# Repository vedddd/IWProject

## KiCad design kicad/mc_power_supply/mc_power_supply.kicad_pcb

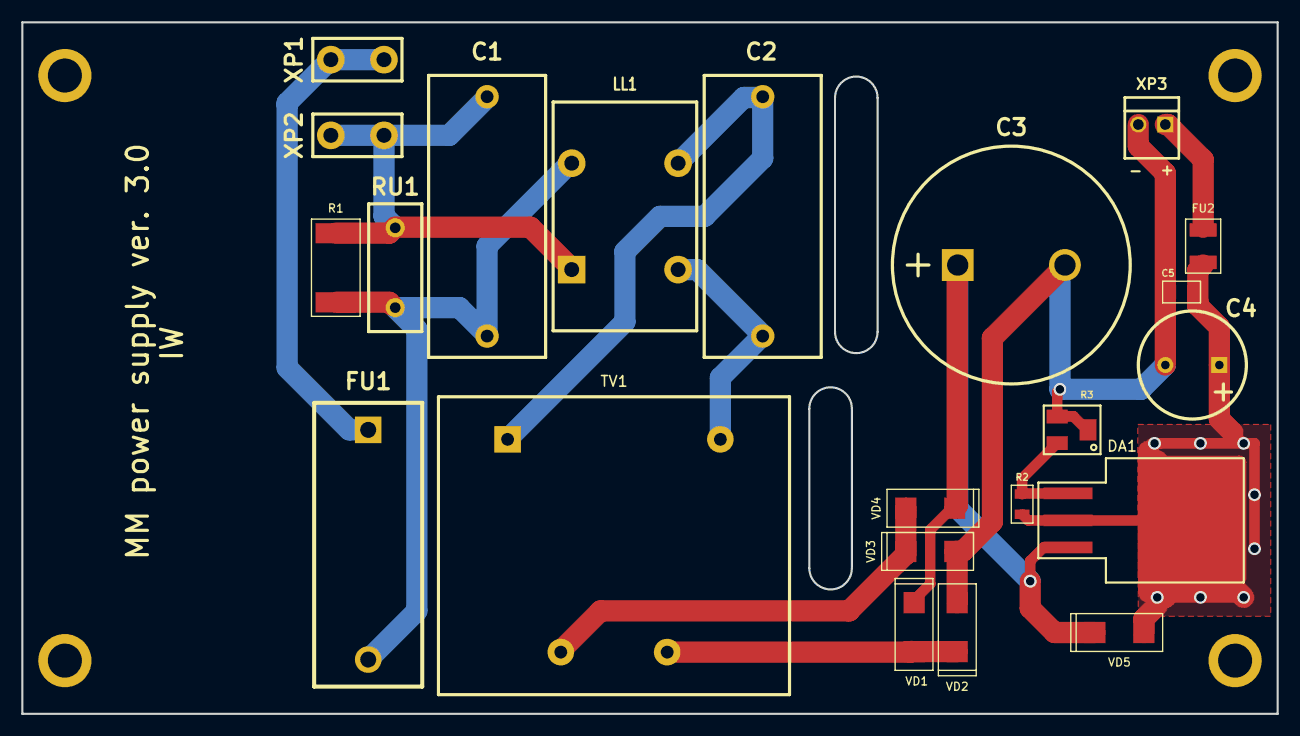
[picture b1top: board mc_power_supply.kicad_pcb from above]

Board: 2 copper layers, 118.0 x 65.0 mm, 26 parts (0 on the bottom side), 12 nets.

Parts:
1_PIN, 1_PIN#2, 1_PIN#3, 1_PIN#4: P***; 1_pin
C1, C2: 1 мк 305В; CAPACITOR_B32923_26.5x11
C3: 4700 мк 35 В; CAPACITOR_10_D22
C4: 470 мк 35 В; CAPACITOR_5.08_D10
C5: 0.1 мк; SMD0805
DA1: LM317KTTR; TO-263-3_TabPin_2
FU1: 0.1 A; FU_PTF15B
FU2: MF-USMF020-2; SMD1210
LL1: B82731T2301A020; EMI_EPCOS_B82731T
R1: 510 к; SMD2512
R2: 240; SMD0805
R3: 5 к; BOURNS_3224W
RU1: B72210S0271K101; RU_EPCOS_B72210S0271K101_12х5
TV1: ТПГ-2-12; TPG2-12
VD1, VD2, VD3, VD4, VD5: VS-10MQ100NTRPBF; SMA
XP1, XP2: L-KLS8-01128-PC-250-0.8; TERMINAL_KLS8-01128_6.3mm
XP3: WF-2

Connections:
/GND: C3.2, C4.2, C5.2, R3.2, R3.3, VD2.1, VD3.1, XP3.2
unnamed: C1.1, FU1.2, LL1.2, R1.2, RU1.1
unnamed: C1.2, LL1.1, R1.1, RU1.2, XP2.1
unnamed: C2.1, LL1.4, TV1.5
unnamed: C2.2, LL1.3, TV1.1
unnamed: C3.1, DA1.3, VD1.2, VD4.2, VD5.2
unnamed: C4.1, C5.1, DA1.2, FU2.1, R2.2, VD5.1
unnamed: DA1.1, R2.1, R3.1
unnamed: FU1.1, XP1.1
unnamed: FU2.2, XP3.1
unnamed: TV1.7, VD1.1, VD2.2
unnamed: TV1.9, VD3.2, VD4.1

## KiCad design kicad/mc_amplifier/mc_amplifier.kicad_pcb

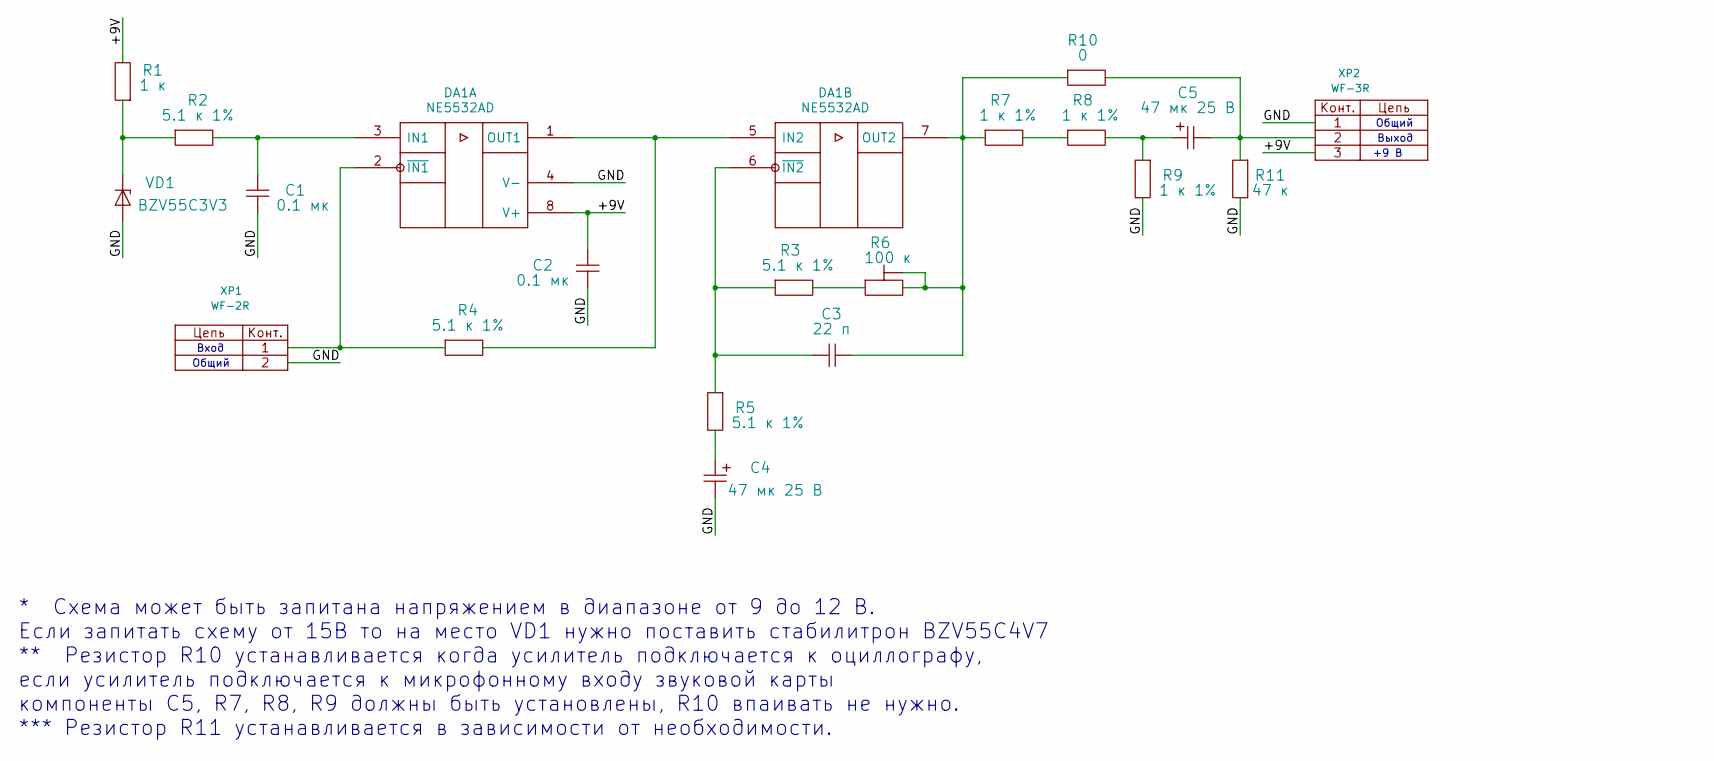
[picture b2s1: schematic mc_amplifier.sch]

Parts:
C1, C2: 0.1 мк; SMD0805
C3: 22 п; SMD0805
C4, C5: 47 мк 25 В; CASE_D
DA1: NE5532AD; SOIC8
R1: 1 к; SMD0805
R2, R3, R4, R5: 5.1 к 1%; SMD0805
R6: 100 к; BOURNS_3224J
R7, R8, R9: 1 к 1%; SMD0805
R10: 0; SMD0805
R11: 47 к; SMD0805
VD1: BZV55C3V3; SOD80C
XP1: WF-2R; WF-2
XP2: WF-3R; WF-3

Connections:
/+9V: C2.1, DA1.8 (V+), R1.2, XP2.3
/GND: C1.2, C2.2, C4.2, DA1.4 (V-), R9.2, R11.2, VD1.1, XP1.2, XP2.1
unnamed: C1.1, DA1.3 (IN1), R2.2
unnamed: C3.1, DA1.7 (OUT2), R6.2, R6.3, R7.1, R10.1
unnamed: C3.2, DA1.6 (~IN2), R3.1, R5.1
unnamed: C4.1, R5.2
unnamed: C5.1, R8.2, R9.1
unnamed: C5.2, R10.2, R11.1, XP2.2
unnamed: DA1.1 (OUT1), DA1.5 (IN2), R4.2
unnamed: DA1.2 (~IN1), R4.1, XP1.1
unnamed: R1.1, R2.1, VD1.2
unnamed: R3.2, R6.1
unnamed: R7.2, R8.1

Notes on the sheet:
Вход
Общий
Выход
+9 В
* Схема может быть запитана напряжением в диапазоне от 9 до 12 В. Если запитать схему от 15В то на место VD1 нужно поставить стабилитрон BZV55C4V7 ** Резистор R10 устанавливается когда усилитель подключается к оциллографу, если усилитель подключается к микрофонному входу звуковой карты компоненты C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

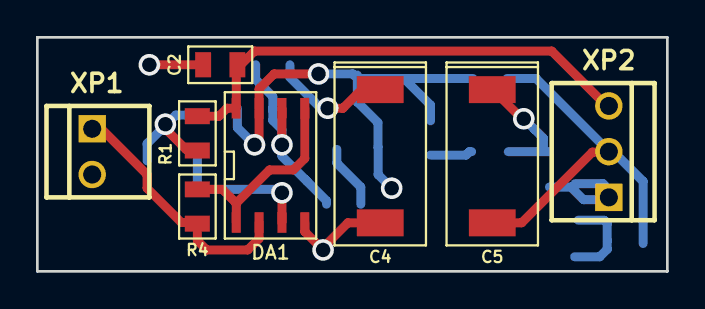
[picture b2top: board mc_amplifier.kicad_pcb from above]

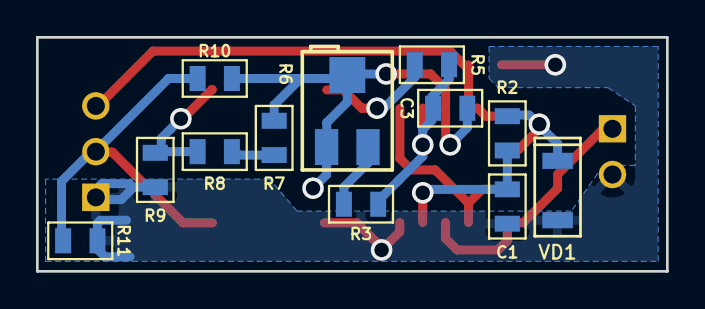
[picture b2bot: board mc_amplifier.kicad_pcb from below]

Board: 2 copper layers, 35.0 x 13.0 mm, 20 parts (12 on the bottom side), 13 nets.

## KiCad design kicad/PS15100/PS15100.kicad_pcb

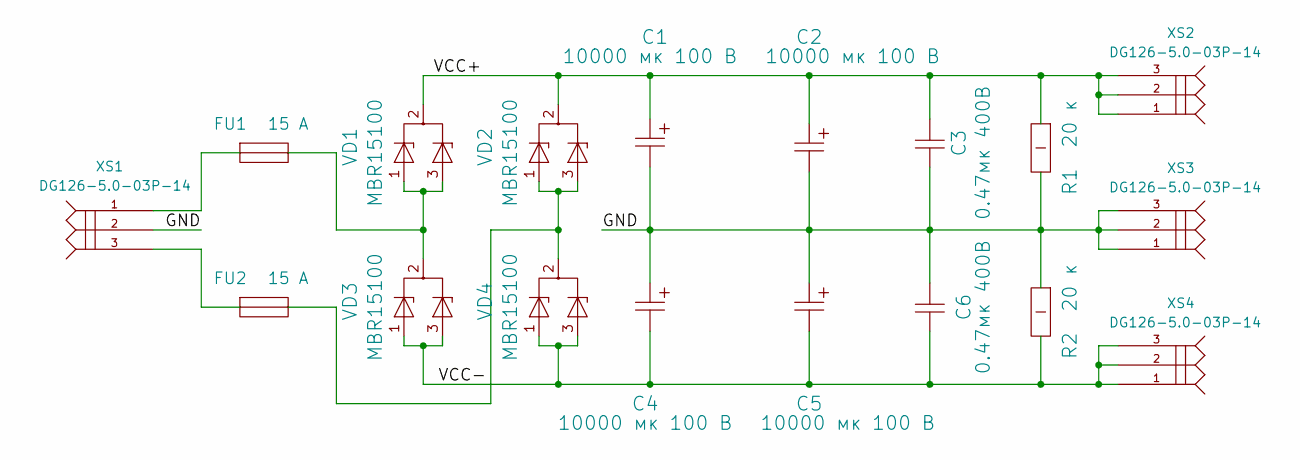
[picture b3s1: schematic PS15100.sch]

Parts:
C1, C2, C4, C5: 10000 мк 100 В; CAPACITOR_10_D36
C3, C6: 0.47мк 400В; K73-17
FU1, FU2: 15 A; FU_PTF15B
R1, R2: 20 к; RESISTOR_1W
VD1, VD2, VD3, VD4: MBR15100; TO220_RAD_16.5x15_VD
XS1, XS2, XS3, XS4: DG126-5.0-03P-14

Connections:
/GND: C1.2, C2.2, C3.1, C4.1, C5.1, C6.2, R1.2, R2.1, XS1.2, XS3.1, XS3.2, XS3.3
/VCC+: C1.1, C2.1, C3.2, R1.1, VD1.2, VD2.2, XS2.1, XS2.2, XS2.3
/VCC-: C4.2, C5.2, C6.1, R2.2, VD3.1, VD3.3, VD4.1, VD4.3, XS4.1, XS4.2, XS4.3
unnamed: FU1.1, XS1.1
unnamed: FU1.2, VD1.1, VD1.3, VD3.2
unnamed: FU2.1, XS1.3
unnamed: FU2.2, VD2.1, VD2.3, VD4.2

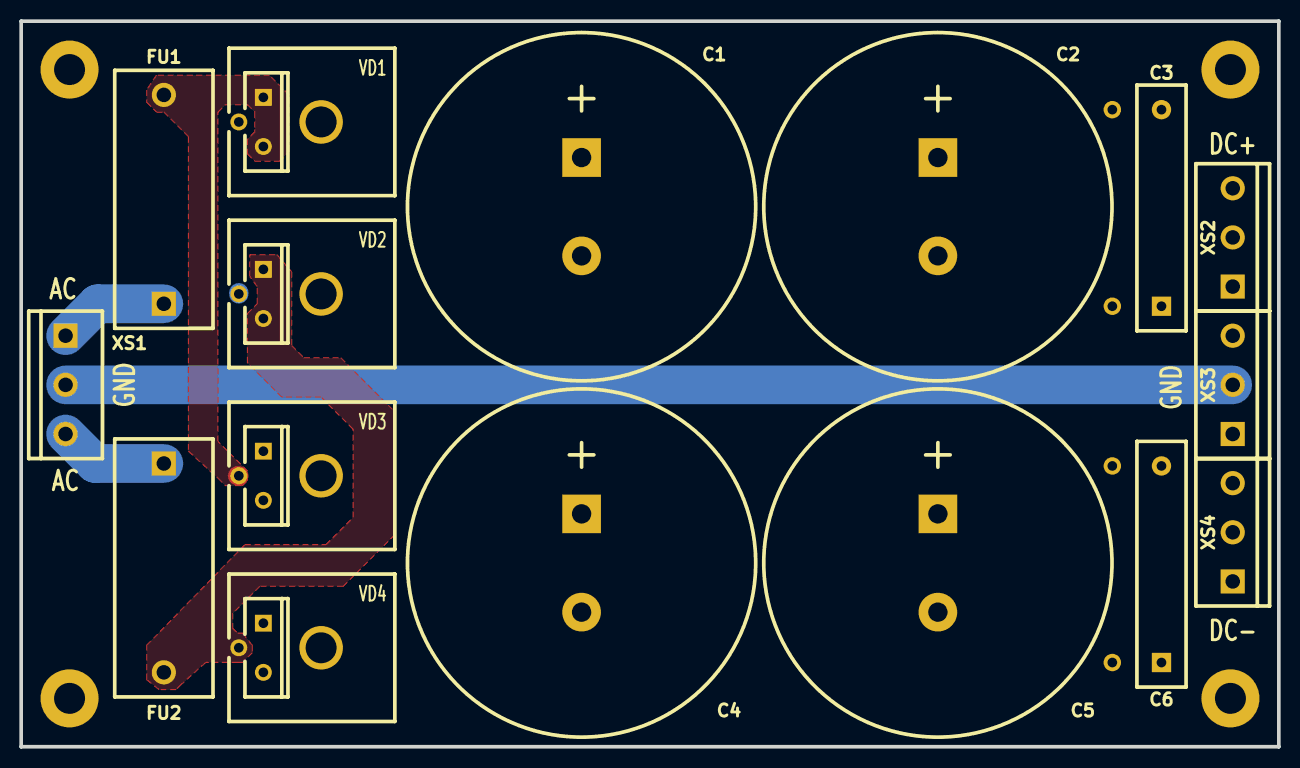
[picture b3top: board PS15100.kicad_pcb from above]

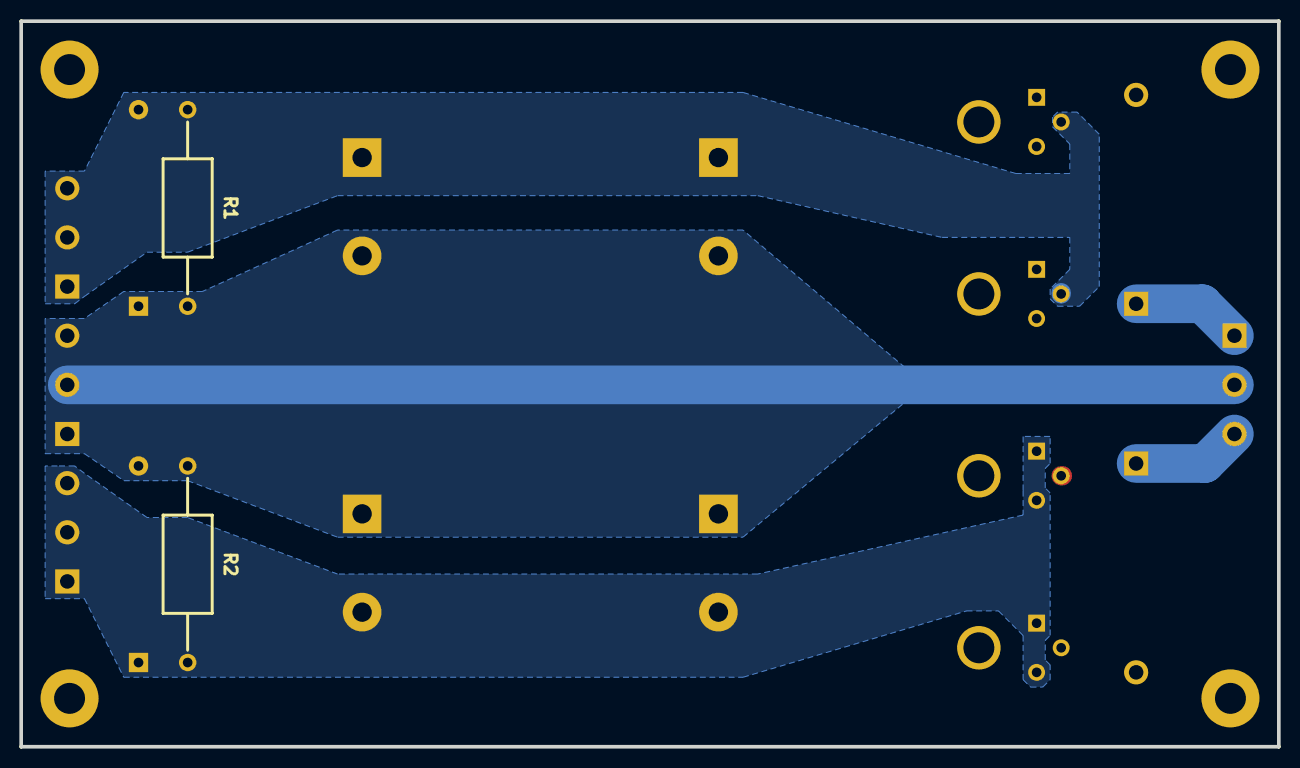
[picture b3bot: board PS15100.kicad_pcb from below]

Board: 2 copper layers, 130.0 x 75.0 mm, 22 parts (2 on the bottom side), 7 nets.

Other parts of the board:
1_PIN, 1_PIN#2, 1_PIN#3, 1_PIN#4: P***; 1_pin

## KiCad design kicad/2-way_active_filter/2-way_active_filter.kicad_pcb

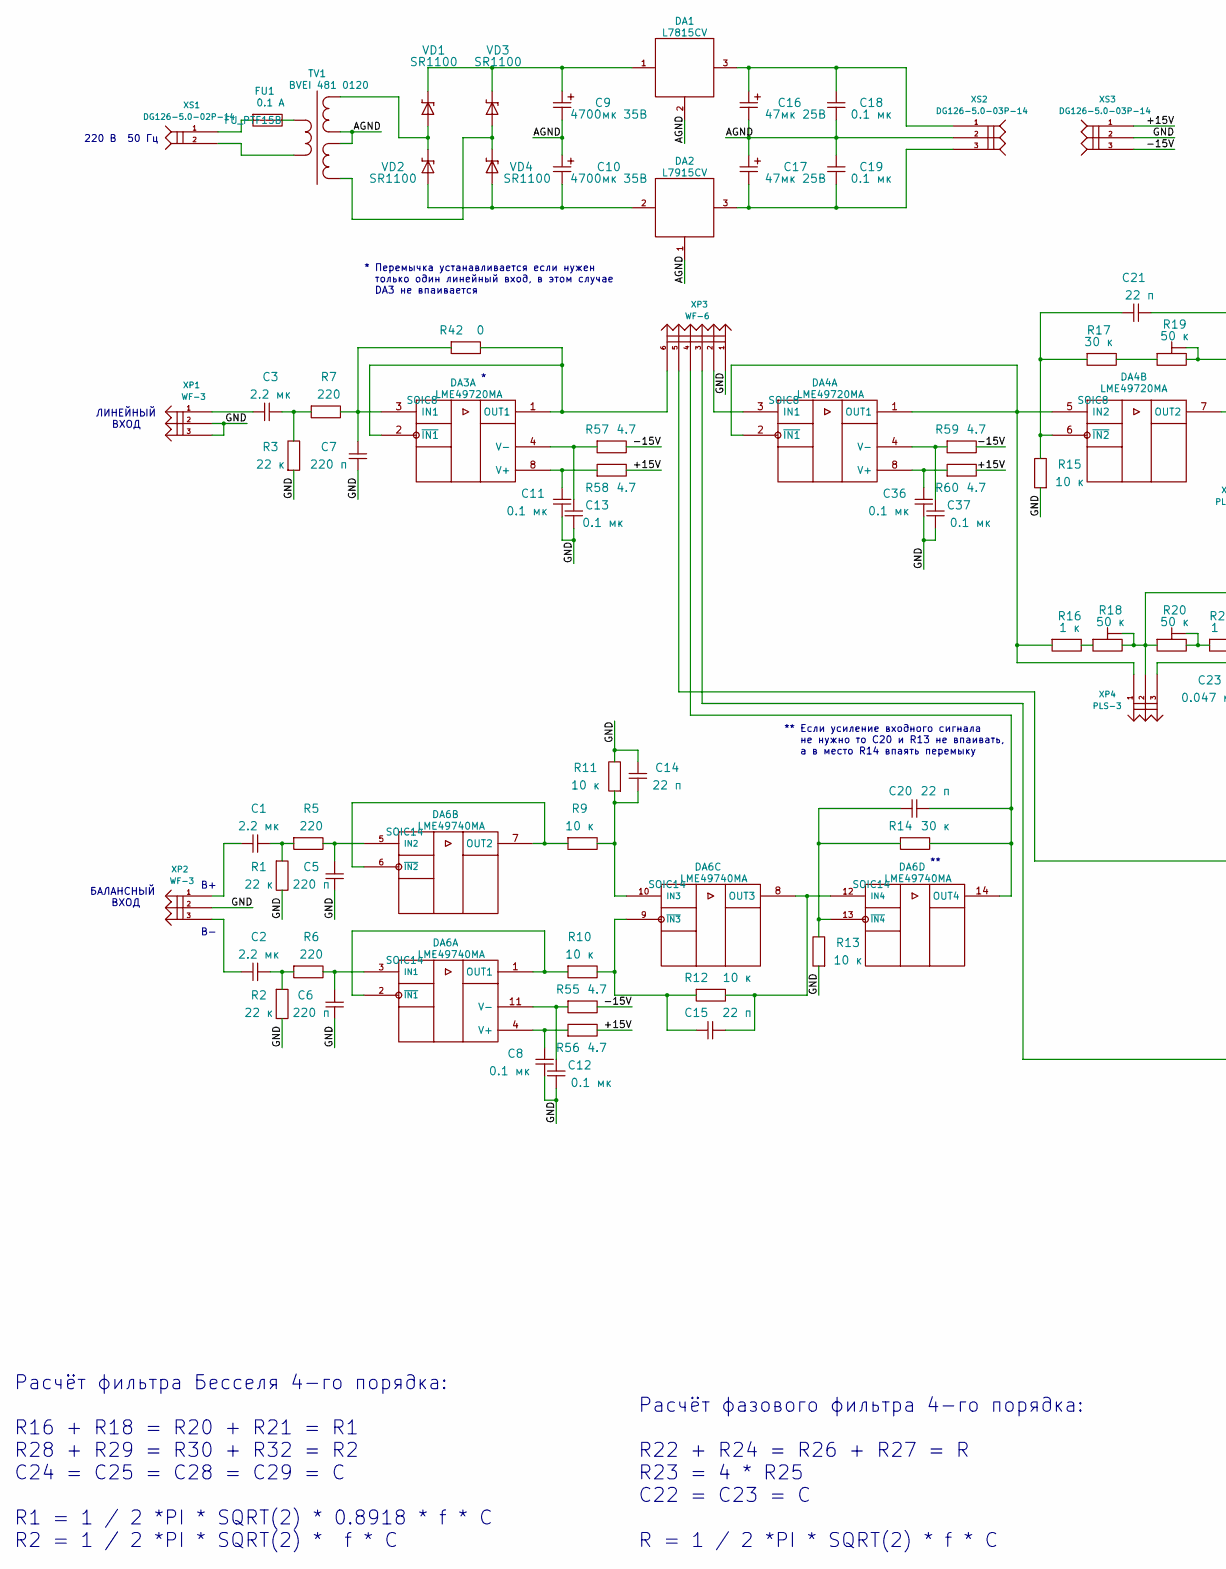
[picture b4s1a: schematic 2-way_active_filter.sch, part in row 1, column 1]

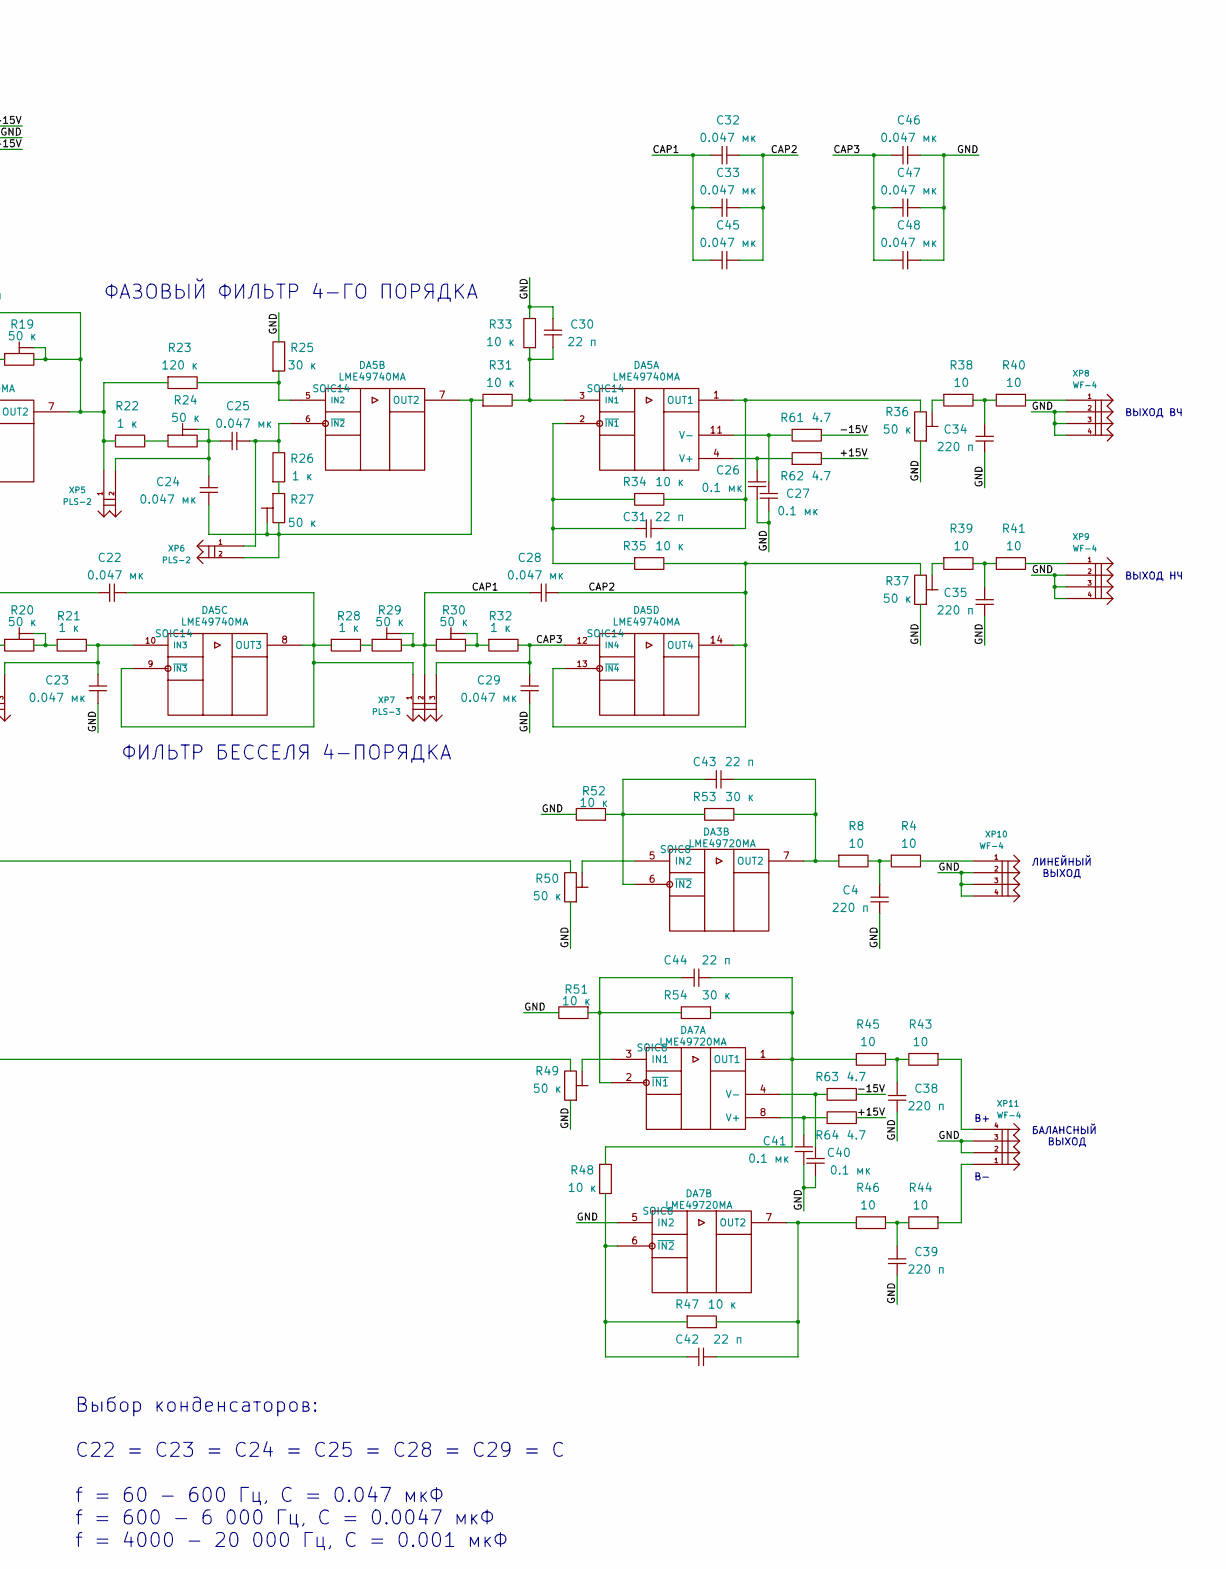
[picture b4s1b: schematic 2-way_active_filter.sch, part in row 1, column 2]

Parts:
C1, C2, C3: 2.2 мк; CAPACITOR_MKP4_27_5_32x11
C4, C5, C6, C7, C34, C35, C38, C39: 220 п; SMD0805
C8, C11, C12, C13, C18, C19, C26, C27, C36, C37, C40, C41: 0.1 мк; SMD0805
C9, C10: 4700мк 35В; CAPACITOR_10_D22
C14, C15, C20, C21, C30, C31, C42, C43, C44: 22 п; SMD0805
C16, C17: 47мк 25В; CAPACITOR_CD263_2.54_D6.3
C22, C23, C24, C25, C28, C29, C32, C33, C45, C46, C47, C48: 0.047 мк; CAPACITOR_FKP2_5_7x6.5
DA1: L7815CV; TO220_RAD_16.5x15
DA2: L7915CV; TO220_RAD_16.5x15
DA3, DA4, DA7: LME49720MA; SOIC8~
DA5, DA6: LME49740MA; SOIC14~
FU1: 0.1 А; FU_PTF15B~
R1, R2, R3: 22 к; SMD0805
R4, R8, R38, R39, R40, R41, R43, R44, R45, R46: 10; SMD0805
R5, R6, R7: 220; SMD0805
R9, R10, R11, R12, R13, R15, R31, R33, R34, R35, R47, R48, R51, R52: 10 к; SMD0805
R14, R17, R25, R53, R54: 30 к; SMD0805
R16, R21, R22, R26, R28, R32: 1 к; SMD0805
R18, R19, R20, R24, R27, R29, R30, R36, R37, R49, R50: 50 к; Electron_3296W
R23: 120 к; SMD0805
R42: 0; SMD0805
R55, R56, R57, R58, R59, R60, R61, R62, R63, R64: 4.7; SMD0805
TV1: BVEI 481 0120; BVEI_481_1120
VD1, VD2, VD3, VD4: SR1100; DO-41
XP1, XP2: WF-3; WF-3~
XP3: WF-6; WF-6~
XP4, XP7: PLS-3; PIN_ARRAY_3x1~
XP5, XP6: PLS-2; PIN_ARRAY_2x1~
XP8, XP9, XP10, XP11: WF-4; WF-4~
XS1: DG126-5.0-02P-14; DG126-5.0-02P-14~
XS2, XS3: DG126-5.0-03P-14; DG126-5.0-03P-14~

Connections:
/+15V: R56.2, R58.2, R60.2, R62.2, R64.2, XS3.1
/-15V: R55.2, R57.2, R59.2, R61.2, R63.2, XS3.3
/AGND: C9.2, C10.1, C16.2, C17.1, C18.2, C19.1, DA1.2 (com), DA2.1 (com), TV1.8, TV1.11, XS2.2
/CAP1: C28.1, C32.1, C33.1, C45.1, R29.2, R29.3, R30.1, XP7.2
/CAP2: C28.2, C32.2, C33.2, C45.2, DA5.13 (~IN4), DA5.14 (OUT4), R35.2, R37.3
/CAP3: C29.1, C46.1, C47.1, C48.1, DA5.12 (IN4), R32.2, XP7.3
/GND: C4.1, C5.1, C6.1, C7.1, C8.2, C11.2, C12.2, C13.2, C14.1, C23.2, C26.2, C27.2, C29.2, C30.1, C34.1, C35.1, C36.2, C37.2, C38.1, C39.1, C40.2, C41.2, C46.2, C47.2, C48.2, DA7.5 (IN2), R1.2, R2.2, R3.1, R11.2, R13.1, R15.1, R25.2, R33.2, R36.1, R37.1, R49.1, R50.1, R51.2, R52.2, XP1.2, XP1.3, XP2.2, XP3.1, XP8.2, XP8.3, XP8.4, XP9.2, XP9.3, XP9.4, XP10.2, XP10.3, XP10.4, XP11.2, XP11.3, XS3.2
unnamed: C1.1, XP2.1
unnamed: C1.2, R1.1, R5.1
unnamed: C2.1, XP2.3
unnamed: C2.2, R2.1, R6.1
unnamed: C3.1, XP1.1
unnamed: C3.2, R3.2, R7.1
unnamed: C4.2, R4.1, R8.2
unnamed: C5.2, DA6.5 (IN2), R5.2
unnamed: C6.2, DA6.3 (IN1), R6.2
unnamed: C7.2, DA3.3 (IN1), R7.2, R42.1
unnamed: C8.1, DA6.4 (V+), R56.1
unnamed: C9.1, DA1.1 (Vin), VD1.2, VD3.2
unnamed: C10.2, DA2.2 (Vin), VD2.1, VD4.1
unnamed: C11.1, DA3.8 (V+), R58.1
unnamed: C12.1, DA6.11 (V-), R55.1
unnamed: C13.1, DA3.4 (V-), R57.1
unnamed: C14.2, DA6.10 (IN3), R9.2, R11.1
unnamed: C15.1, DA6.9 (~IN3), R10.2, R12.1
unnamed: C15.2, DA6.8 (OUT3), DA6.12 (IN4), R12.2
unnamed: C16.1, C18.1, DA1.3 (Vout), XS2.1
unnamed: C17.2, C19.2, DA2.3 (Vout), XS2.3
unnamed: C20.1, DA6.13 (~IN4), R13.2, R14.1
unnamed: C20.2, DA6.14 (OUT4), R14.2, XP3.4
unnamed: C21.1, DA4.6 (~IN2), R15.2, R17.1
unnamed: C21.2, DA4.7 (OUT2), R19.2, R19.3, R22.1, R23.1, XP5.1
unnamed: C22.1, R18.2, R18.3, R20.1, XP4.2
unnamed: C22.2, DA5.8 (OUT3), DA5.9 (~IN3), R28.1, XP7.1
unnamed: C23.1, DA5.10 (IN3), R21.2, XP4.3
unnamed: C24.1, C25.1, R24.2, R24.3, XP5.2
unnamed: C24.2, DA5.7 (OUT2), R27.2, R27.3, R31.1, XP6.2
unnamed: C25.2, DA5.6 (~IN2), R26.2, XP6.1
unnamed: C26.1, DA5.4 (V+), R62.1
unnamed: C27.1, DA5.11 (V-), R61.1
unnamed: C30.2, DA5.3 (IN1), R31.2, R33.1
unnamed: C31.1, DA5.2 (~IN1), R34.1, R35.1
unnamed: C31.2, DA5.1 (OUT1), R34.2, R36.3
unnamed: C34.2, R38.2, R40.1
unnamed: C35.2, R39.2, R41.1
unnamed: C36.1, DA4.8 (V+), R60.1
unnamed: C37.1, DA4.4 (V-), R59.1
unnamed: C38.2, R43.2, R45.1
unnamed: C39.2, R44.2, R46.1
unnamed: C40.1, DA7.4 (V-), R63.1
unnamed: C41.1, DA7.8 (V+), R64.1
unnamed: C42.1, DA7.6 (~IN2), R47.1, R48.2
unnamed: C42.2, DA7.7 (OUT2), R46.2, R47.2
unnamed: C43.1, DA3.6 (~IN2), R52.1, R53.1
unnamed: C43.2, DA3.7 (OUT2), R8.1, R53.2
unnamed: C44.1, DA7.1 (OUT1), R45.2, R48.1, R54.1
unnamed: C44.2, DA7.2 (~IN1), R51.1, R54.2
unnamed: DA3.1 (OUT1), DA3.2 (~IN1), R42.2, XP3.6
unnamed: DA3.5 (IN2), R50.2
unnamed: DA4.1 (OUT1), DA4.2 (~IN1), DA4.5 (IN2), R16.1, XP4.1
unnamed: DA4.3 (IN1), XP3.2
unnamed: DA5.5 (IN2), R23.2, R25.1
unnamed: DA6.1 (OUT1), DA6.2 (~IN1), R10.1
unnamed: DA6.6 (~IN2), DA6.7 (OUT2), R9.1
unnamed: DA7.3 (IN1), R49.2
unnamed: FU1.1, XS1.1
unnamed: FU1.2, TV1.1
unnamed: R4.2, XP10.1
unnamed: R16.2, R18.1
unnamed: R17.2, R19.1
unnamed: R20.2, R20.3, R21.1
unnamed: R22.2, R24.1
unnamed: R26.1, R27.1
unnamed: R28.2, R29.1
unnamed: R30.2, R30.3, R32.1
unnamed: R36.2, R38.1
unnamed: R37.2, R39.1
unnamed: R40.2, XP8.1
unnamed: R41.2, XP9.1
unnamed: R43.1, XP11.4
unnamed: R44.1, XP11.1
unnamed: R49.3, XP3.3
unnamed: R50.3, XP3.5
unnamed: TV1.6, XS1.2
unnamed: TV1.7, VD3.1, VD4.2
unnamed: TV1.12, VD1.1, VD2.2

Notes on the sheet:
ФИЛЬТР БЕССЕЛЯ 4-ПОРЯДКА
220 В 50 Гц
ФАЗОВЫЙ ФИЛЬТР 4-ГО ПОРЯДКА
ВЫХОД ВЧ
ВЫХОД НЧ
Расчёт фазового фильтра 4-го порядка: R22 + R24 = R26 + R27 = R R23 = 4 * R25 C22 = C23 = C R = 1 / 2 *PI * SQRT(2) * f * C
Расчёт фильтра Бесселя 4-го порядка: R16 + R18 = R20 + R21 = R1 R28 + R29 = R30 + R32 = R2 C24 = C25 = C28 = C29 = C R1 = 1 / 2 *PI * SQRT(2) * 0.8918 * f * C R2 = 1 / 2 *PI * SQRT(2) * f * C
Выбор конденсаторов: C22 = C23 = C24 = C25 = C28 = C29 = C f = 60 - 600 Гц, C = 0.047 мкФ f = 600 - 6 000 Гц, C = 0.0047 мкФ f = 4000 - 20 000 Гц, C = 0.001 мкФ
ЛИНЕЙНЫЙ ВХОД
БАЛАНСНЫЙ ВХОД
* Перемычка устанавливается если нужен только один линейный вход, в этом случае DA3 не впаивается
БАЛАНСНЫЙ ВЫХОД
ЛИНЕЙНЫЙ ВЫХОД
** Если усиление входного сигнала не нужно то C20 и R13 не впаивать, а в место R14 впаять перемыку

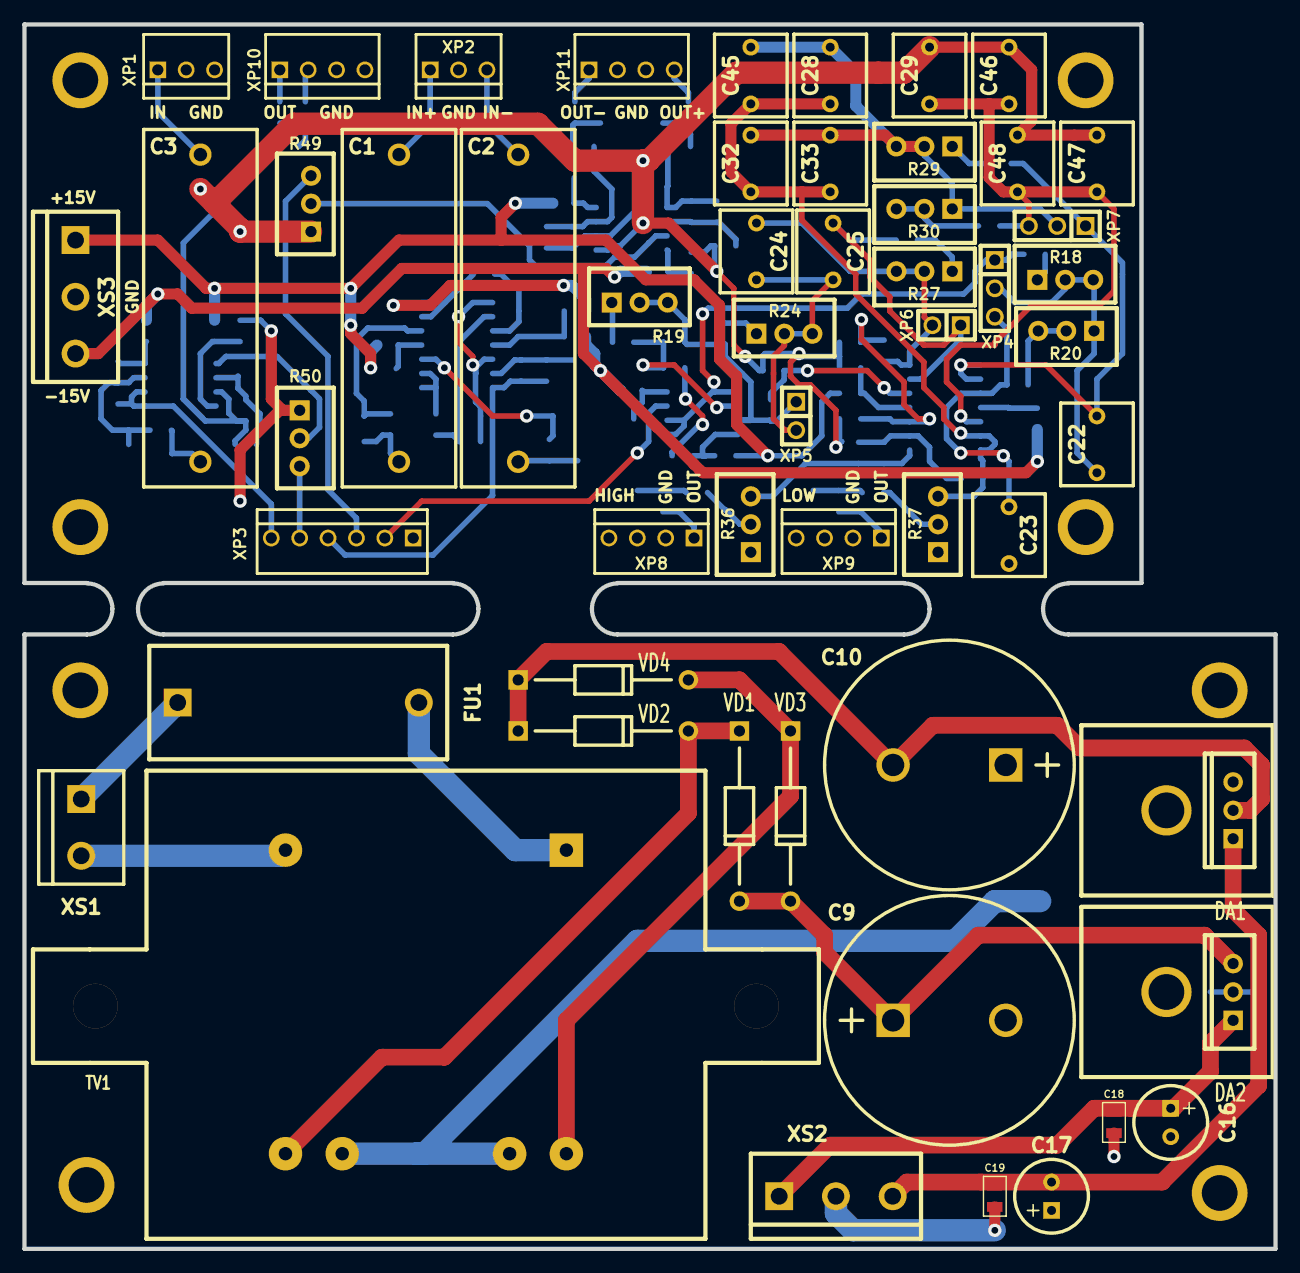
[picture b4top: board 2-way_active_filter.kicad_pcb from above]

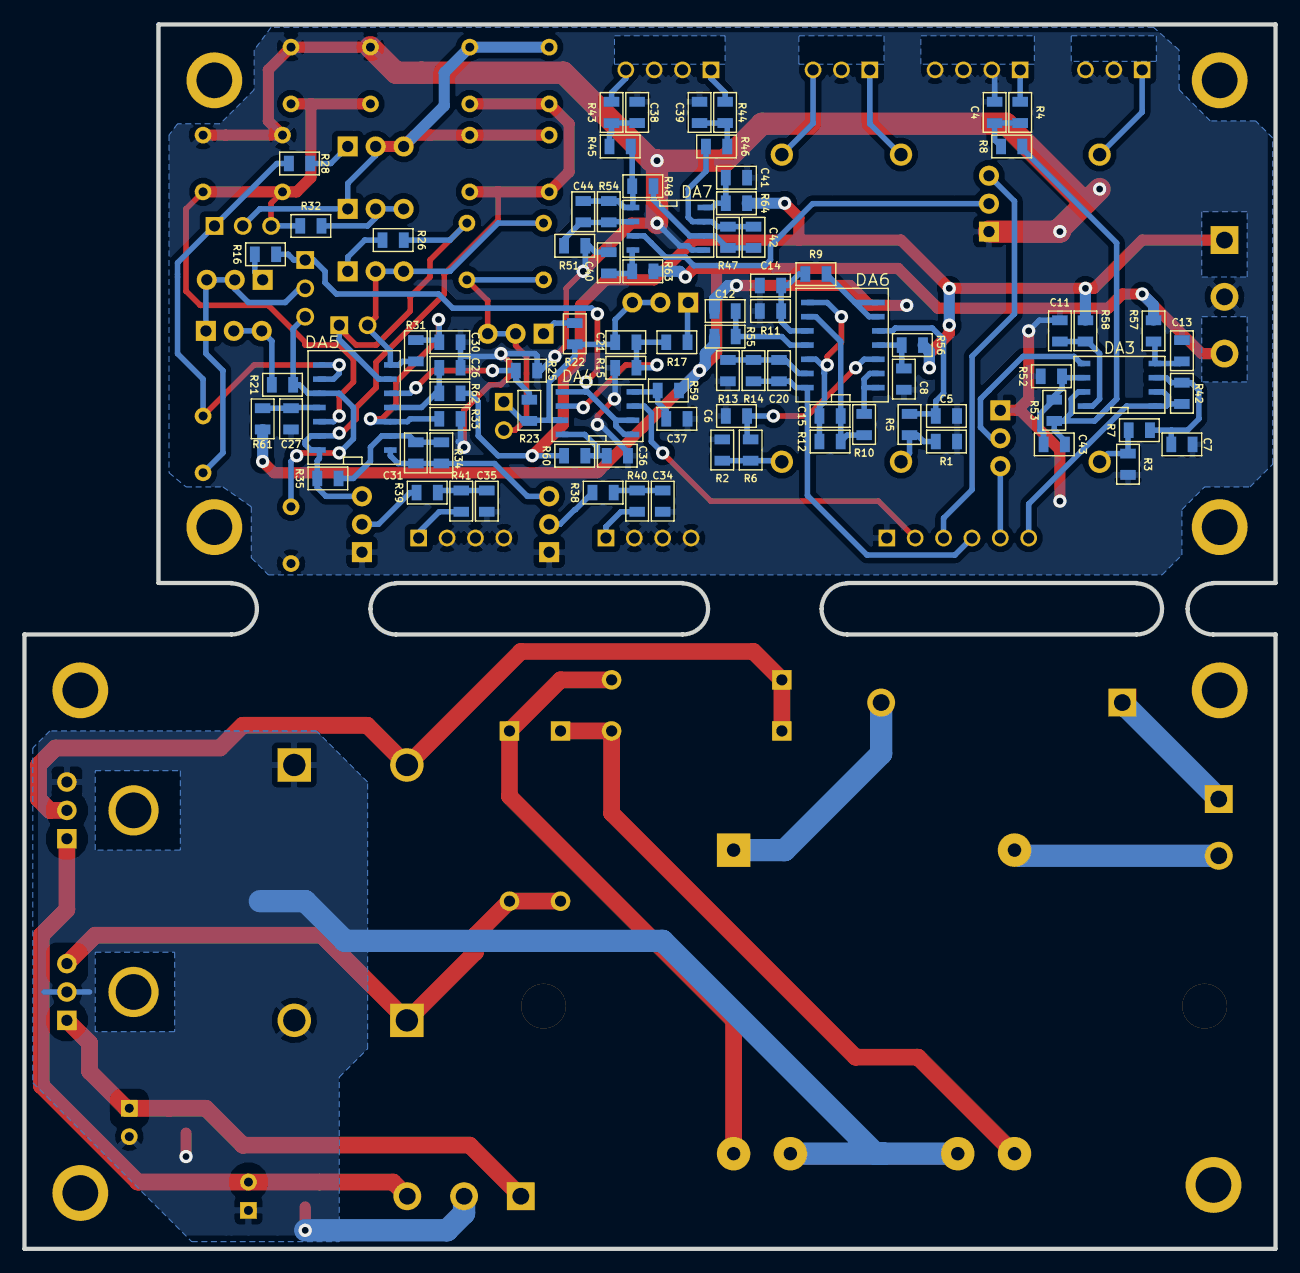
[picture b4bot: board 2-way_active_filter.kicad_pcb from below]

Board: 2 copper layers, 112.0 x 109.6 mm, 147 parts (85 on the bottom side), 86 nets.

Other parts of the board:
1_PIN, 1_PIN#2, 1_PIN#3, 1_PIN#4, 1_PIN#5, 1_PIN#6, 1_PIN#7, 1_PIN#8: P***; 1_pin

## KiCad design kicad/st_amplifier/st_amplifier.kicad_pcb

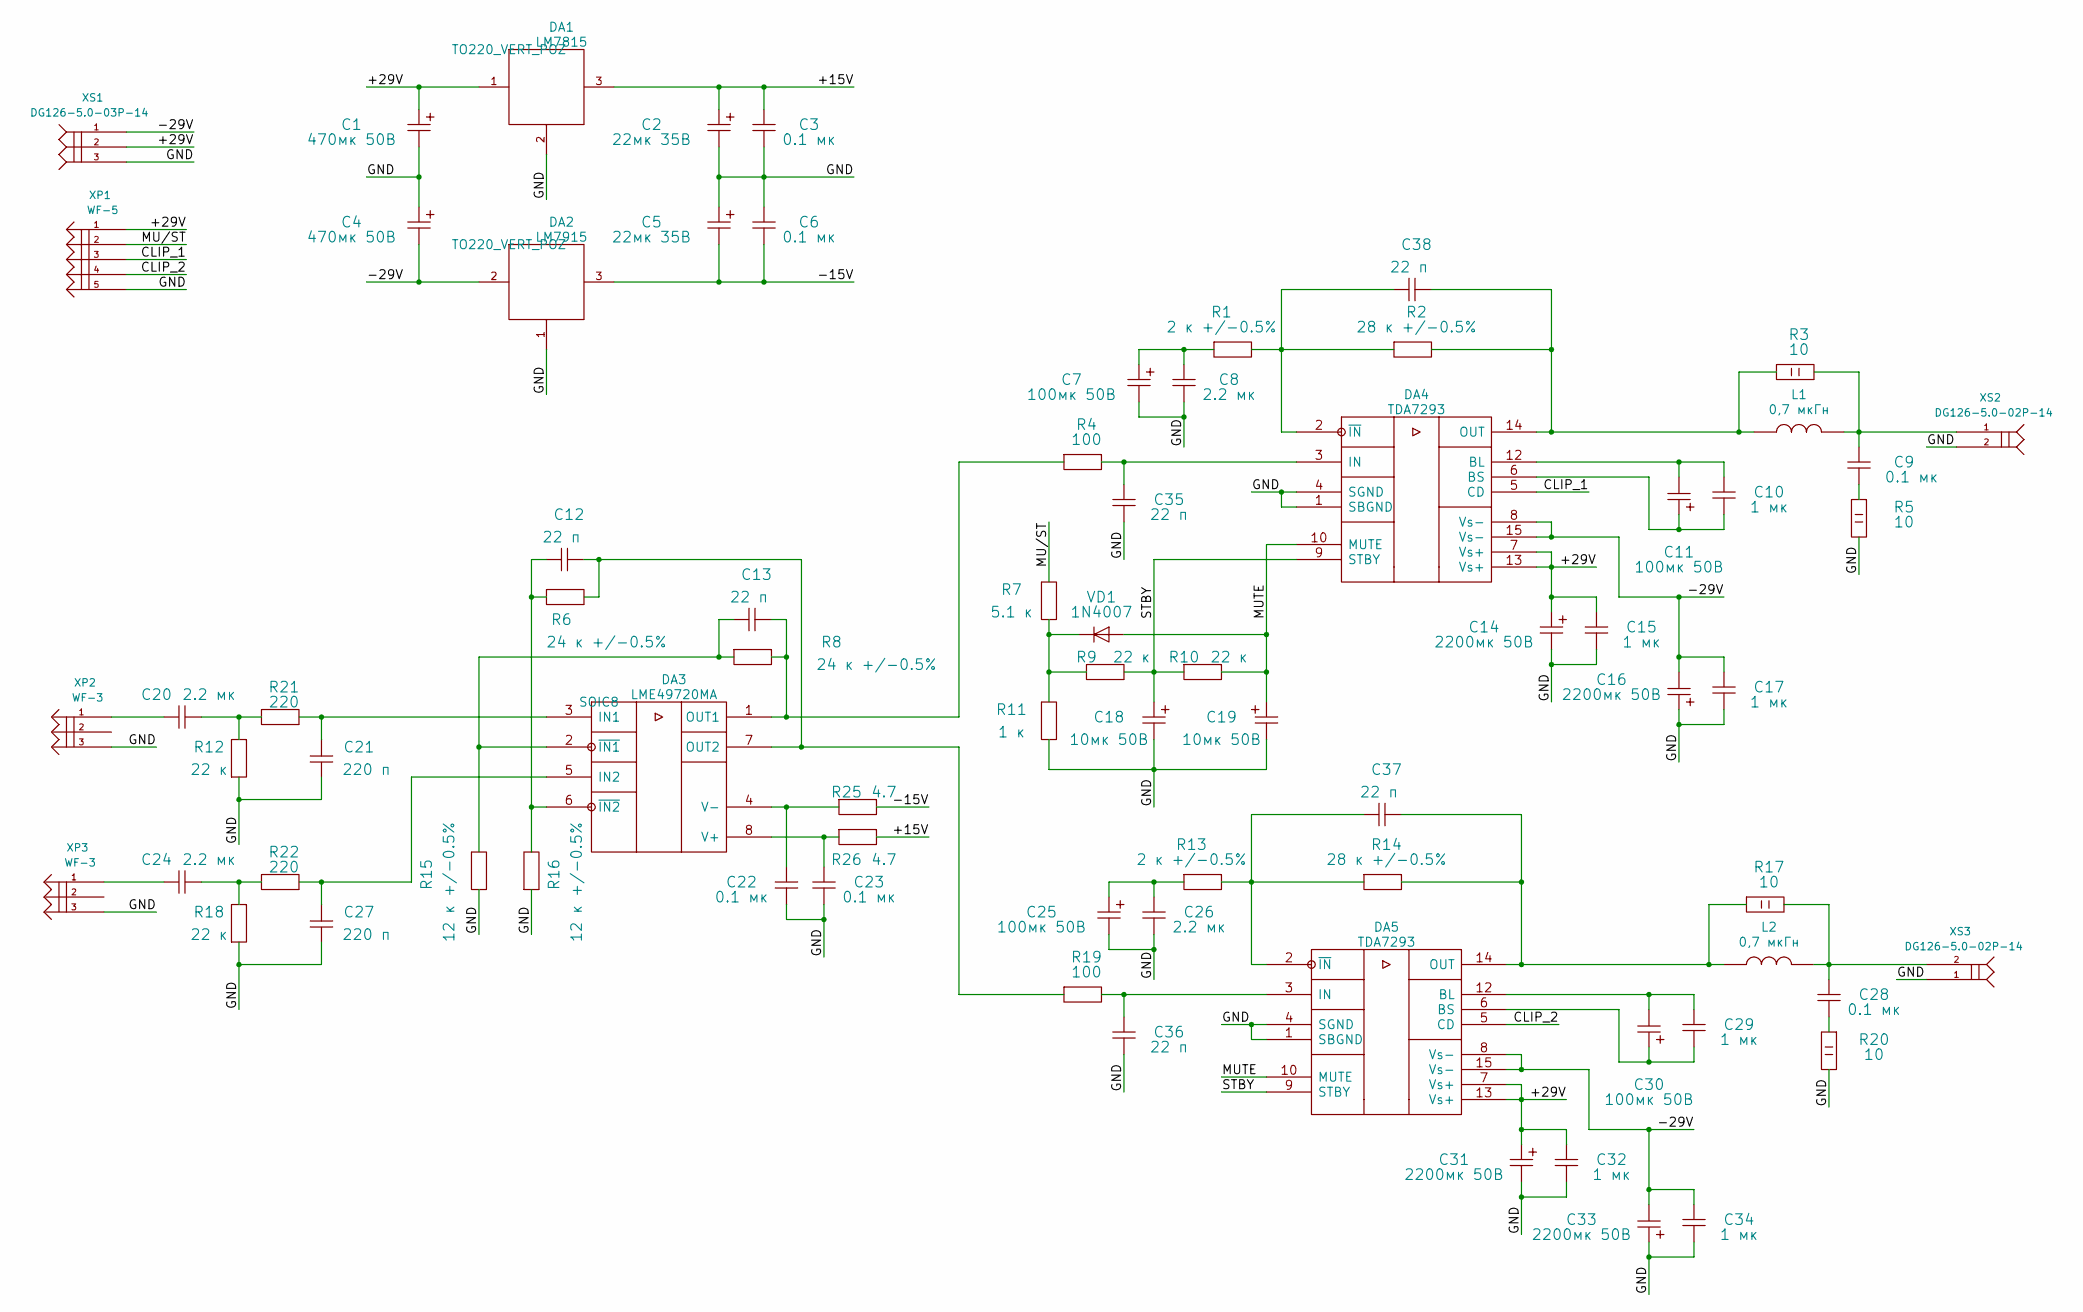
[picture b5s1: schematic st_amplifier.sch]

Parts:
C1, C4: 470мк 50В; CAPACITOR_CD263_5.08_D10
C2, C5: 22мк 35В; CAPACITOR_CD263_2.54_D6.3
C3, C6, C22, C23: 0.1 мк; SMD0805
C7, C11, C25, C30: 100мк 50В; CAPACITOR_5.08_D13
C8, C20, C24, C26: 2.2 мк; CAPACITOR_CBB21_20_24x11
C9, C28: 0.1 мк; CAPACITOR_CBB21_10_12x6
C10, C15, C17, C29, C32, C34: 1 мк; CAPACITOR_CBB21_15_16x6
C12, C13, C35, C36, C37, C38: 22 п; SMD0805
C14, C16, C31, C33: 2200мк 50В; CAPACITOR_10_D22
C18, C19: 10мк 50В; CAPACITOR_0511
C21, C27: 220 п; SMD0805
DA1: LM7815; TO220_VERT_POZ~
DA2: LM7915; TO220_VERT_POZ~
DA3: LME49720MA; SOIC8~
DA4, DA5: TDA7293; MULTIWATT15
L1, L2: 0,7 мкГн; INDUCTORS_1_15x8
R1, R13: 2 к +/-0.5%; SMD1206
R2, R14: 28 к +/-0.5%; SMD1206
R3, R5, R17, R20: 10; RESISTOR_2W
R4, R19: 100; SMD0805
R6, R8: 24 к +/-0.5%; SMD0805
R7: 5.1 к; SMD0805
R9, R10, R12, R18: 22 к; SMD0805
R11: 1 к; SMD0805
R15, R16: 12 к +/-0.5%; SMD0805
R21, R22: 220; SMD0805
R25, R26: 4.7; SMD0805
VD1: 1N4007; DO-41
XP1: WF-5; WF-5~
XP2, XP3: WF-3; WF-3~
XS1: DG126-5.0-03P-14; DG126-5.0-03P-14~
XS2, XS3: DG126-5.0-02P-14; DG126-5.0-02P-14~

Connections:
/+15V: C2.1, C3.1, DA1.3 (Vout), R26.2
/+29V: C1.1, C14.1, C15.1, C31.1, C32.1, DA1.1 (Vin), DA4.7 (Vs+), DA4.13 (Vs+), DA5.7 (Vs+), DA5.13 (Vs+), XP1.1, XS1.2
/-15V: C5.2, C6.2, DA2.3 (Vout), R25.2
/-29V: C4.2, C16.2, C17.1, C33.2, C34.1, DA2.2 (Vin), DA4.8 (Vs-), DA4.15 (Vs-), DA5.8 (Vs-), DA5.15 (Vs-), XS1.1
/CLIP_1: DA4.5 (CD), XP1.3
/CLIP_2: DA5.5 (CD), XP1.4
/GND: C1.2, C2.2, C3.2, C4.1, C5.1, C6.1, C7.2, C8.2, C14.2, C15.2, C16.1, C17.2, C18.2, C19.2, C21.1, C22.2, C23.2, C25.2, C26.2, C27.1, C31.2, C32.2, C33.1, C34.2, C35.2, C36.2, DA1.2 (com), DA2.1 (com), DA4.1 (SBGND), DA4.4 (SGND), DA5.1 (SBGND), DA5.4 (SGND), R5.2, R11.1, R12.1, R15.1, R16.1, R18.1, R20.2, XP1.5, XP2.3, XP3.3, XS1.3, XS2.2, XS3.1
/MU/ST: R7.2, XP1.2
/MUTE: C19.1, DA4.10 (MUTE), DA5.10 (MUTE), R10.2, VD1.1
/STBY: C18.1, DA4.9 (STBY), DA5.9 (STBY), R9.2, R10.1
unnamed: C7.1, C8.1, R1.1
unnamed: C9.1, L1.1, R3.2, XS2.1
unnamed: C9.2, R5.1
unnamed: C10.1, C11.2, DA4.12 (BL)
unnamed: C10.2, C11.1, DA4.6 (BS)
unnamed: C12.1, DA3.6 (~IN2), R6.1, R16.2
unnamed: C12.2, DA3.7 (OUT2), R6.2, R19.1
unnamed: C13.1, DA3.2 (~IN1), R8.1, R15.2
unnamed: C13.2, DA3.1 (OUT1), R4.1, R8.2
unnamed: C20.1, XP2.1
unnamed: C20.2, R12.2, R21.1
unnamed: C21.2, DA3.3 (IN1), R21.2
unnamed: C22.1, DA3.4 (V-), R25.1
unnamed: C23.1, DA3.8 (V+), R26.1
unnamed: C24.1, XP3.1
unnamed: C24.2, R18.2, R22.1
unnamed: C25.1, C26.1, R13.1
unnamed: C27.2, DA3.5 (IN2), R22.2
unnamed: C28.1, L2.1, R17.2, XS3.2
unnamed: C28.2, R20.1
unnamed: C29.1, C30.2, DA5.12 (BL)
unnamed: C29.2, C30.1, DA5.6 (BS)
unnamed: C35.1, DA4.3 (IN), R4.2
unnamed: C36.1, DA5.3 (IN), R19.2
unnamed: C37.1, DA5.2 (~IN), R13.2, R14.1
unnamed: C37.2, DA5.14 (OUT), L2.2, R14.2, R17.1
unnamed: C38.1, DA4.2 (~IN), R1.2, R2.1
unnamed: C38.2, DA4.14 (OUT), L1.2, R2.2, R3.1
unnamed: R7.1, R9.1, R11.2, VD1.2
